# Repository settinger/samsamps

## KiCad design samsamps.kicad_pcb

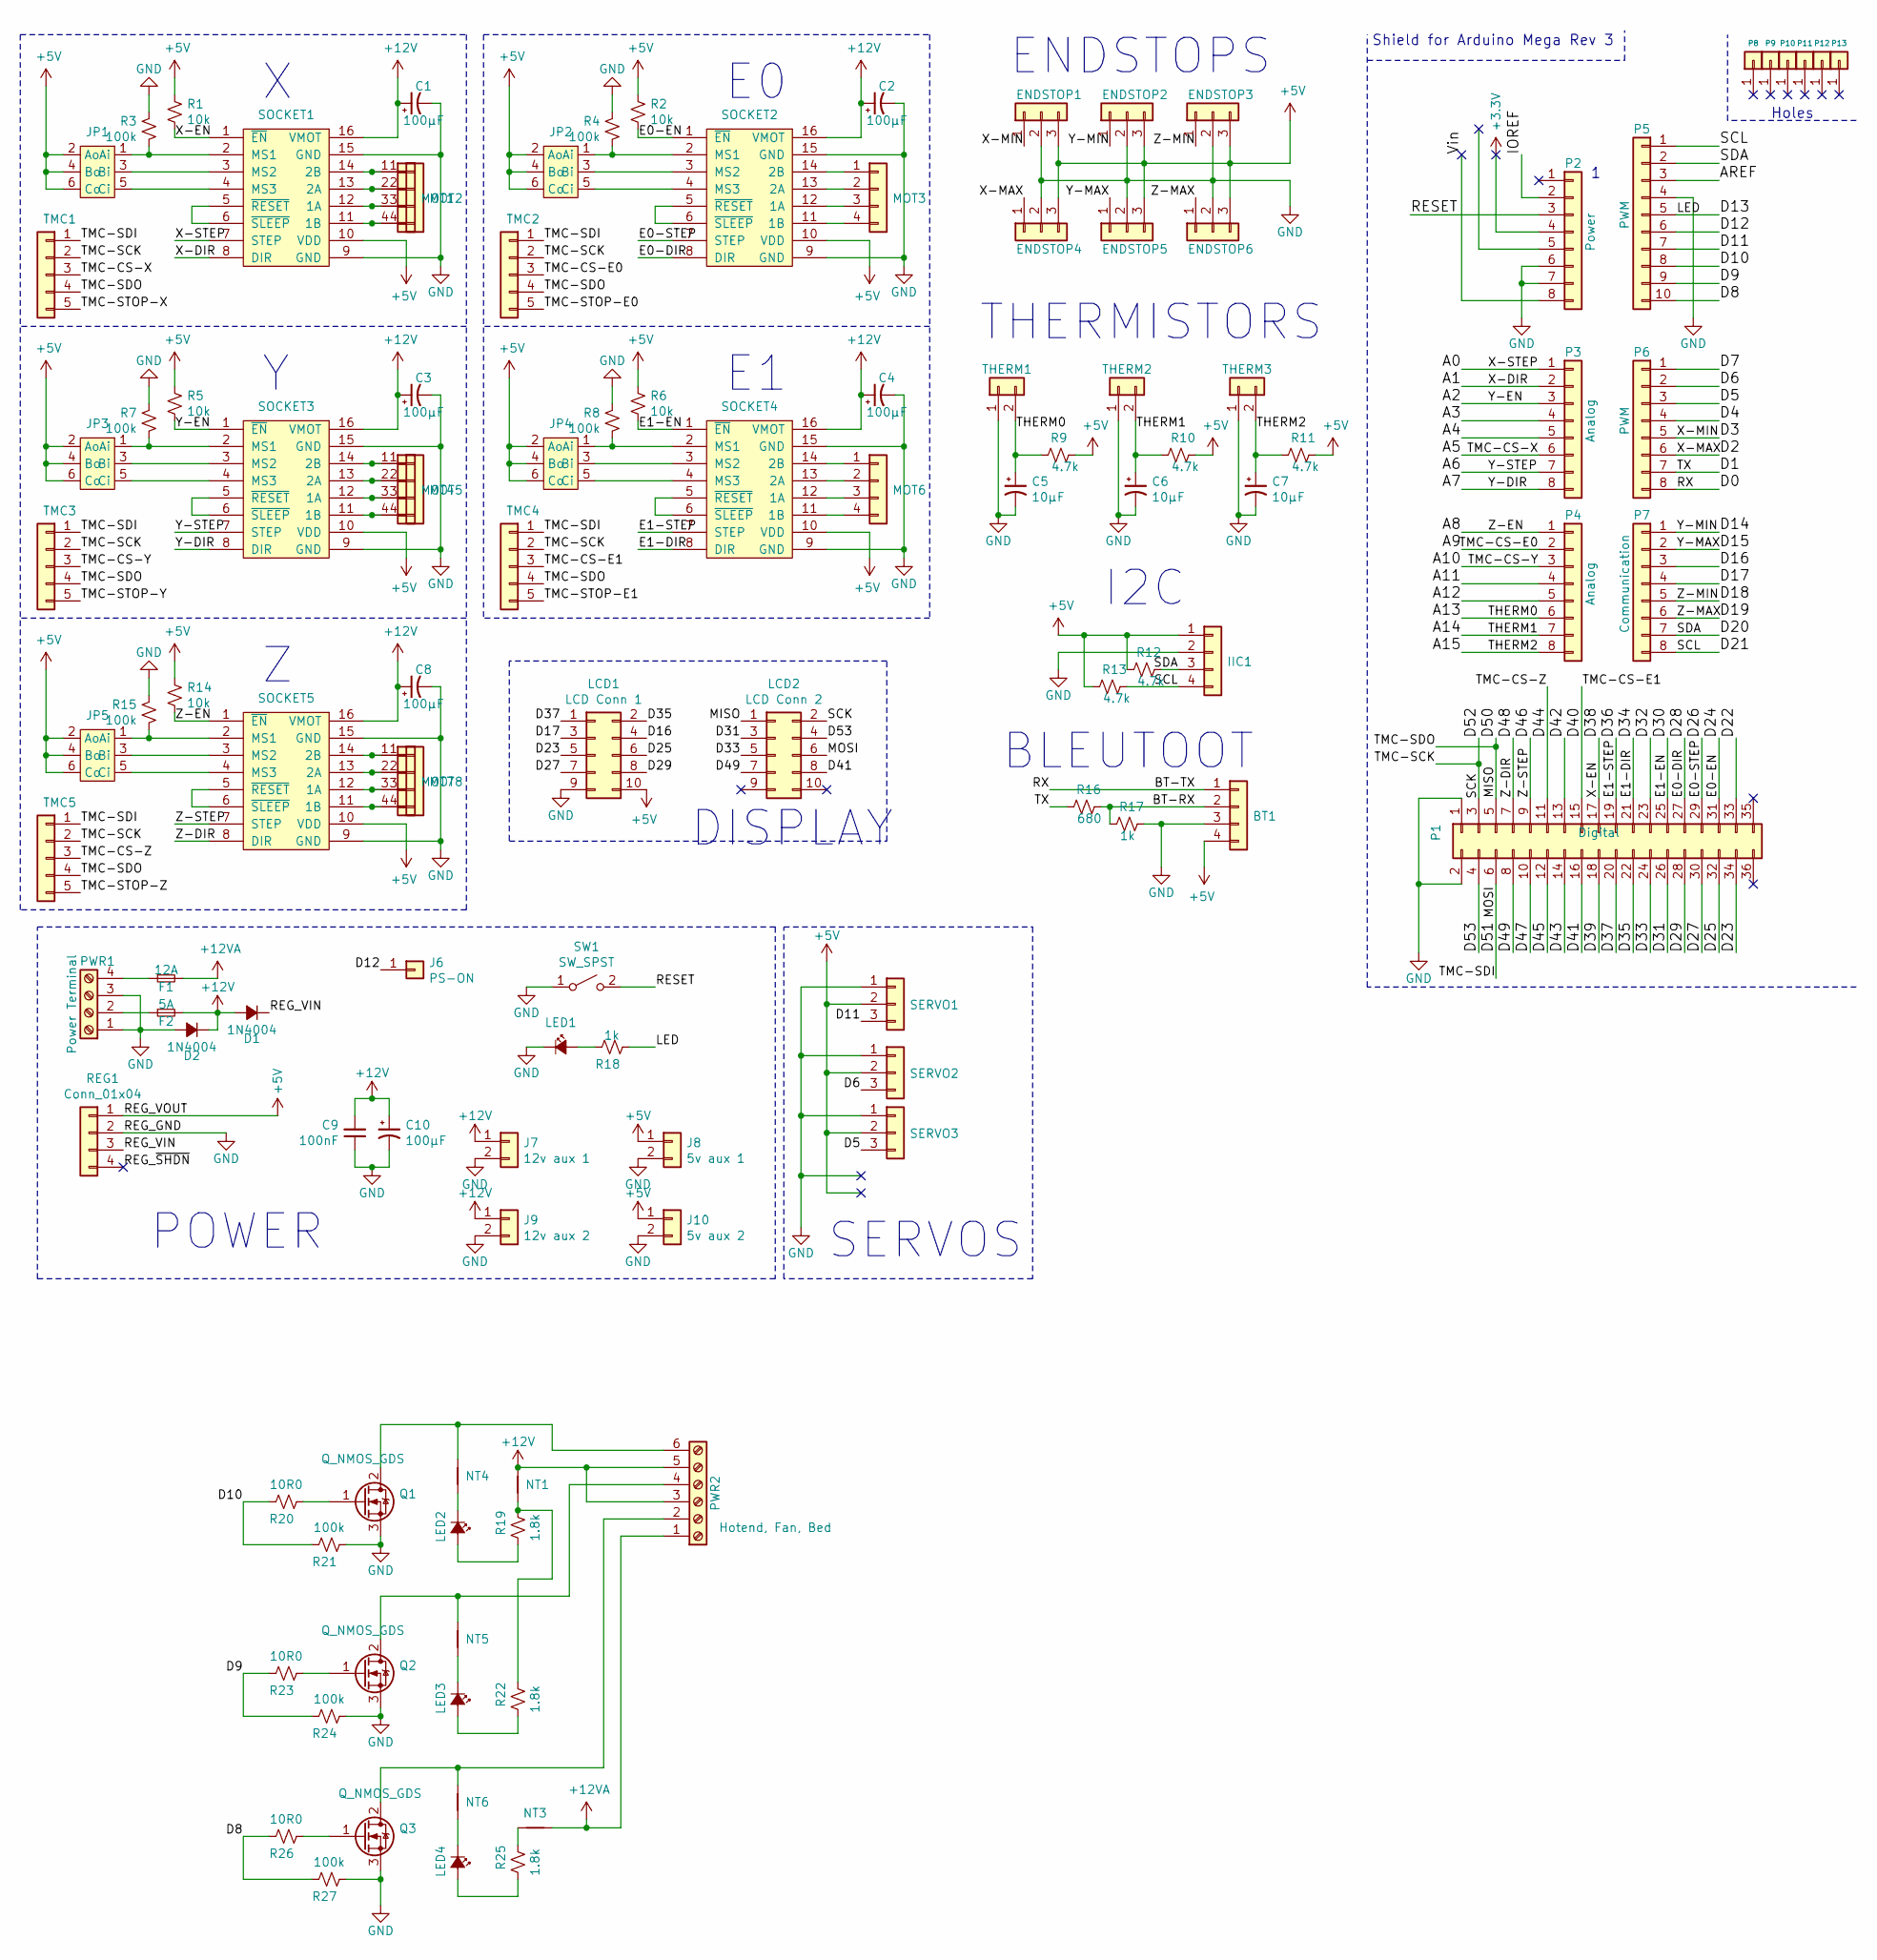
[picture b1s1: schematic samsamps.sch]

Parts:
BT1: Conn_01x04; Socket_Strip_Straight_1x04_Pitch2.54mm
C1, C2, C3, C4, C8, C10: 100μF; CP_Radial_D6.3mm_P2.50mm
C5, C6, C7: 10μF; CP_Radial_D6.3mm_P2.50mm
C9: 100nF; C_Rect_L7.0mm_W2.0mm_P5.00mm
D1, D2: 1N4004; D_5W_P10.16mm_Horizontal
ENDSTOP1, ENDSTOP2, ENDSTOP3, ENDSTOP4, ENDSTOP5, ENDSTOP6: Conn_01x03; Pin_Header_Straight_1x03_Pitch2.54mm
F1: 12A; Fuseholder5x20_horiz_SemiClosed_Casing10x25mm
F2: 5A; Fuseholder5x20_horiz_SemiClosed_Casing10x25mm
IIC1: Conn_01x04; Socket_Strip_Straight_1x04_Pitch2.54mm
J6: PS-ON; Pin_Header_Straight_1x01_Pitch2.54mm
J7: 12v aux 1; Socket_Strip_Straight_1x02_Pitch2.54mm
J8: 5v aux 1; Socket_Strip_Straight_1x02_Pitch2.54mm
J9: 12v aux 2; Socket_Strip_Straight_1x02_Pitch2.54mm
J10: 5v aux 2; Socket_Strip_Straight_1x02_Pitch2.54mm
JP1, JP2, JP3, JP4, JP5: jumpers; Pin_Header_Straight_2x03_Pitch2.54mm
LCD1: LCD Conn 1; Multicomp_MC9A12-1034_2x05x2.54mm_Straight
LCD2: LCD Conn 2; Multicomp_MC9A12-1034_2x05x2.54mm_Straight
LED1, LED2, LED3, LED4: LED_Small_ALT; LED_D3.0mm
MOT1, MOT2, MOT3, MOT4, MOT5, MOT6, MOT7, MOT8: Conn_01x04; Socket_Strip_Straight_1x04_Pitch2.54mm
NT1, NT3, NT4, NT5, NT6: Net-Tie_2; NetTie-2_SMD_Pad0.5mm
P1: Digital; Socket_Strip_Arduino_2x18
P2: Power; Socket_Strip_Arduino_1x08
P3, P4: Analog; Socket_Strip_Arduino_1x08
P5: PWM; Socket_Strip_Arduino_1x10
P6: PWM; Socket_Strip_Arduino_1x08
P7: Communication; Socket_Strip_Arduino_1x08
P8, P9, P10, P11, P12, P13: CONN_01X01; Arduino_1pin
PWR1: Power Terminal; TerminalBlock_4_P9.5mm
PWR2: Hotend, Fan, Bed; TerminalBlock_6_P9.5mm
Q1, Q2, Q3: Q_NMOS_GDS; TO-220-3_Vertical
R1, R2, R5, R6, R14: 10k; R_Axial_DIN0204_L3.6mm_D1.6mm_P7.62mm_Horizontal
R3, R4, R7, R8, R15, R21, R24, R27: 100k; R_Axial_DIN0204_L3.6mm_D1.6mm_P7.62mm_Horizontal
R9, R10, R11, R12, R13: 4.7k; R_Axial_DIN0204_L3.6mm_D1.6mm_P7.62mm_Horizontal
R16: 680; R_Axial_DIN0204_L3.6mm_D1.6mm_P7.62mm_Horizontal
R17, R18: 1k; R_Axial_DIN0204_L3.6mm_D1.6mm_P7.62mm_Horizontal
R19, R22, R25: 1.8k; R_Axial_DIN0204_L3.6mm_D1.6mm_P7.62mm_Horizontal
R20, R23, R26: 10R0; R_Axial_DIN0204_L3.6mm_D1.6mm_P7.62mm_Horizontal
REG1: Conn_01x04; Socket_Strip_Straight_1x04_Pitch2.54mm
SERVO1, SERVO2, SERVO3: Conn_01x03; Socket_Strip_Straight_1x03_Pitch2.54mm
SOCKET1, SOCKET2, SOCKET3, SOCKET4, SOCKET5: stepper_driver_socket; Stepper_Motor_Driver_Socket
SW1: SW_SPST; SW_PUSH_6mm
THERM1, THERM2, THERM3: Conn_01x02; Pin_Header_Straight_1x02_Pitch2.54mm
TMC1, TMC2, TMC3, TMC4, TMC5: Conn_01x05; Pin_Header_Straight_1x05_Pitch2.54mm

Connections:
+3V3: P2.4
+5V: BT1.4, ENDSTOP1.3, ENDSTOP2.3, ENDSTOP3.3, ENDSTOP4.3, ENDSTOP5.3, ENDSTOP6.3, IIC1.1, J8.1, J10.1, JP1.2 (Ao), JP1.4 (Bo), JP1.6 (Co), JP2.2 (Ao), JP2.4 (Bo), JP2.6 (Co), JP3.2 (Ao), JP3.4 (Bo), JP3.6 (Co), JP4.2 (Ao), JP4.4 (Bo), JP4.6 (Co), JP5.2 (Ao), JP5.4 (Bo), JP5.6 (Co), LCD1.10, R1.1, R2.1, R5.1, R6.1, R9.1, R10.1, R11.1, R12.2, R13.2, R14.1, REG1.1, SERVO1.2, SERVO2.2, SERVO3.2, SOCKET1.10 (VDD), SOCKET2.10 (VDD), SOCKET3.10 (VDD), SOCKET4.10 (VDD), SOCKET5.10 (VDD)
+12V: C1.1, C2.1, C3.1, C4.1, C8.1, C9.2, C10.1, D1.2 (A), D2.1 (K), F2.2, J7.1, J9.1, NT1.1, PWR2.3, PWR2.5, SOCKET1.16 (VMOT), SOCKET2.16 (VMOT), SOCKET3.16 (VMOT), SOCKET4.16 (VMOT), SOCKET5.16 (VMOT); also elsewhere on the board
+12VA: F1.2, NT3.2, PWR2.1
/A0: P3.1, SOCKET1.7 (STEP)
/A1: P3.2, SOCKET1.8 (DIR)
/A2: P3.3, R5.2, SOCKET3.1 (~EN)
/A3: P3.4
/A4: P3.5
/A5: P3.6, TMC1.3
/A6: P3.7, SOCKET3.7 (STEP)
/A7: P3.8, SOCKET3.8 (DIR)
/A8: P4.1, R14.2, SOCKET5.1 (~EN)
/A9: P4.2, TMC2.3
/A10: P4.3, TMC3.3
/A11: P4.4
/A12: P4.5
/A13: C5.1, P4.6, R9.2, THERM1.2
/A14: C6.1, P4.7, R10.2, THERM2.2
/A15: C7.1, P4.8, R11.2, THERM3.2
/AREF: P5.3
/BT-RX: BT1.2, R16.1, R17.2
/BT-TX: BT1.1, P6.8
/D1: P6.7, R16.2
/D2: ENDSTOP4.1, P6.6
/D3: ENDSTOP1.1, P6.5
/D4: P6.4
/D5: P6.3, SERVO3.3
/D6: P6.2, SERVO2.3
/D7: P6.1
/D8: P5.10, R26.1, R27.1
/D9: P5.9, R23.1, R24.1
/D10: P5.8, R20.1, R21.1
/D11: P5.7, SERVO1.3
/D12: J6.1, P5.6
/D13: P5.5, R18.2
/D14: ENDSTOP2.1, P7.1
/D15: ENDSTOP5.1, P7.2
/D16: LCD1.4, P7.3
/D17: LCD1.3, P7.4
/D18: ENDSTOP3.1, P7.5
/D19: ENDSTOP6.1, P7.6
/D20: IIC1.3, P5.2, P7.7, R12.1
/D21: IIC1.4, P5.1, P7.8, R13.1
/D22: P1.33
/D23: LCD1.5, P1.34
/D24: P1.31, R2.2, SOCKET2.1 (~EN)
/D25: LCD1.6, P1.32
/D26: P1.29, SOCKET2.7 (STEP)
/D27: LCD1.7, P1.30
/D28: P1.27, SOCKET2.8 (DIR)
/D29: LCD1.8, P1.28
/D30: P1.25, R6.2, SOCKET4.1 (~EN)
/D31: LCD2.3, P1.26
/D32: P1.23
/D33: LCD2.5, P1.24
/D34: P1.21, SOCKET4.8 (DIR)
/D35: LCD1.2, P1.22
/D36: P1.19, SOCKET4.7 (STEP)
/D37: LCD1.1, P1.20
/D38: P1.17, R1.2, SOCKET1.1 (~EN)
/D39: P1.18
/D40: P1.15, TMC4.3
/D41: LCD2.8, P1.16
/D42: P1.13
/D43: P1.14
/D44: P1.11, TMC5.3
/D45: P1.12
/D46: P1.9, SOCKET5.7 (STEP)
/D47: P1.10
/D48: P1.7, SOCKET5.8 (DIR)
/D49: LCD2.7, P1.8
/D50: LCD2.1, P1.5, TMC1.4, TMC2.4, TMC3.4, TMC4.4, TMC5.4
/D51: LCD2.6, P1.6, TMC1.1, TMC2.1, TMC3.1, TMC4.1, TMC5.1
/D52: LCD2.2, P1.3, TMC1.2, TMC2.2, TMC3.2, TMC4.2, TMC5.2
/D53: LCD2.4, P1.4
/IOREF: P2.2
/REG_VIN: D1.1 (K), REG1.3
/REG_~SHDN: REG1.4
/RESET: P2.3, SW1.2 (B)
/TMC-STOP-E0: TMC2.5
/TMC-STOP-E1: TMC4.5
/TMC-STOP-X: TMC1.5
/TMC-STOP-Y: TMC3.5
/TMC-STOP-Z: TMC5.5
/Vin: P2.8
GND: BT1.3, C1.2, C2.2, C3.2, C4.2, C5.2, C6.2, C7.2, C8.2, C9.1, C10.2, D2.2 (A), ENDSTOP1.2, ENDSTOP2.2, ENDSTOP3.2, ENDSTOP4.2, ENDSTOP5.2, ENDSTOP6.2, IIC1.2, J7.2, J8.2, J9.2, J10.2, LCD1.9, LED1.1 (K), P1.1, P1.2, P2.6, P2.7, P5.4, PWR1.1, PWR1.3, Q1.3 (S), Q2.3 (S), Q3.3 (S), R3.2, R4.2, R7.2, R8.2, R15.2, R17.1, R21.2, R24.2, R27.2, REG1.2, SERVO1.1, SERVO2.1, SERVO3.1, SOCKET1.9 (GND), SOCKET1.15 (GND), SOCKET2.9 (GND), SOCKET2.15 (GND), SOCKET3.9 (GND), SOCKET3.15 (GND), SOCKET4.9 (GND), SOCKET4.15 (GND), SOCKET5.9 (GND), SOCKET5.15 (GND), SW1.1 (A), THERM1.1, THERM2.1, THERM3.1
unnamed: F1.1, PWR1.4
unnamed: F2.1, PWR1.2
unnamed: JP1.1 (Ai), R3.1, SOCKET1.2 (MS1)
unnamed: JP1.3 (Bi), SOCKET1.3 (MS2)
unnamed: JP1.5 (Ci), SOCKET1.4 (MS3)
unnamed: JP2.1 (Ai), R4.1, SOCKET2.2 (MS1)
unnamed: JP2.3 (Bi), SOCKET2.3 (MS2)
unnamed: JP2.5 (Ci), SOCKET2.4 (MS3)
unnamed: JP3.1 (Ai), R7.1, SOCKET3.2 (MS1)
unnamed: JP3.3 (Bi), SOCKET3.3 (MS2)
unnamed: JP3.5 (Ci), SOCKET3.4 (MS3)
unnamed: JP4.1 (Ai), R8.1, SOCKET4.2 (MS1)
unnamed: JP4.3 (Bi), SOCKET4.3 (MS2)
unnamed: JP4.5 (Ci), SOCKET4.4 (MS3)
unnamed: JP5.1 (Ai), R15.1, SOCKET5.2 (MS1)
unnamed: JP5.3 (Bi), SOCKET5.3 (MS2)
unnamed: JP5.5 (Ci), SOCKET5.4 (MS3)
unnamed: LED1.2 (A), R18.1
unnamed: LED2.1 (K), NT4.2
unnamed: LED2.2 (A), R19.2
unnamed: LED3.1 (K), NT5.2
unnamed: LED3.2 (A), R22.2
unnamed: LED4.1 (K), NT6.2
unnamed: LED4.2 (A), R25.2
unnamed: MOT1.1, MOT2.1, SOCKET1.14 (2B)
unnamed: MOT1.2, MOT2.2, SOCKET1.13 (2A)
unnamed: MOT1.3, MOT2.3, SOCKET1.12 (1A)
unnamed: MOT1.4, MOT2.4, SOCKET1.11 (1B)
unnamed: MOT3.1, SOCKET2.14 (2B)
unnamed: MOT3.2, SOCKET2.13 (2A)
unnamed: MOT3.3, SOCKET2.12 (1A)
unnamed: MOT3.4, SOCKET2.11 (1B)
unnamed: MOT4.1, MOT5.1, SOCKET3.14 (2B)
unnamed: MOT4.2, MOT5.2, SOCKET3.13 (2A)
unnamed: MOT4.3, MOT5.3, SOCKET3.12 (1A)
unnamed: MOT4.4, MOT5.4, SOCKET3.11 (1B)
unnamed: MOT6.1, SOCKET4.14 (2B)
unnamed: MOT6.2, SOCKET4.13 (2A)
unnamed: MOT6.3, SOCKET4.12 (1A)
unnamed: MOT6.4, SOCKET4.11 (1B)
unnamed: MOT7.1, MOT8.1, SOCKET5.14 (2B)
unnamed: MOT7.2, MOT8.2, SOCKET5.13 (2A)
unnamed: MOT7.3, MOT8.3, SOCKET5.12 (1A)
unnamed: MOT7.4, MOT8.4, SOCKET5.11 (1B)
unnamed 133: NT1.2, R19.1, R22.1; also elsewhere on the board
unnamed: NT3.1, R25.1
unnamed: NT4.1, PWR2.6, Q1.2 (D)
unnamed: NT5.1, PWR2.4, Q2.2 (D)
unnamed: NT6.1, PWR2.2, Q3.2 (D)
unnamed: Q1.1 (G), R20.2
unnamed: Q2.1 (G), R23.2
unnamed: Q3.1 (G), R26.2
unnamed: SOCKET1.5 (~RESET), SOCKET1.6 (~SLEEP)
unnamed: SOCKET2.5 (~RESET), SOCKET2.6 (~SLEEP)
unnamed: SOCKET3.5 (~RESET), SOCKET3.6 (~SLEEP)
unnamed: SOCKET4.5 (~RESET), SOCKET4.6 (~SLEEP)
unnamed: SOCKET5.5 (~RESET), SOCKET5.6 (~SLEEP)

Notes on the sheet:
Shield for Arduino Mega Rev 3
Holes
POWER
DISPLAY
SERVOS
ENDSTOPS
THERMISTORS
I2C
BLEUTOOT

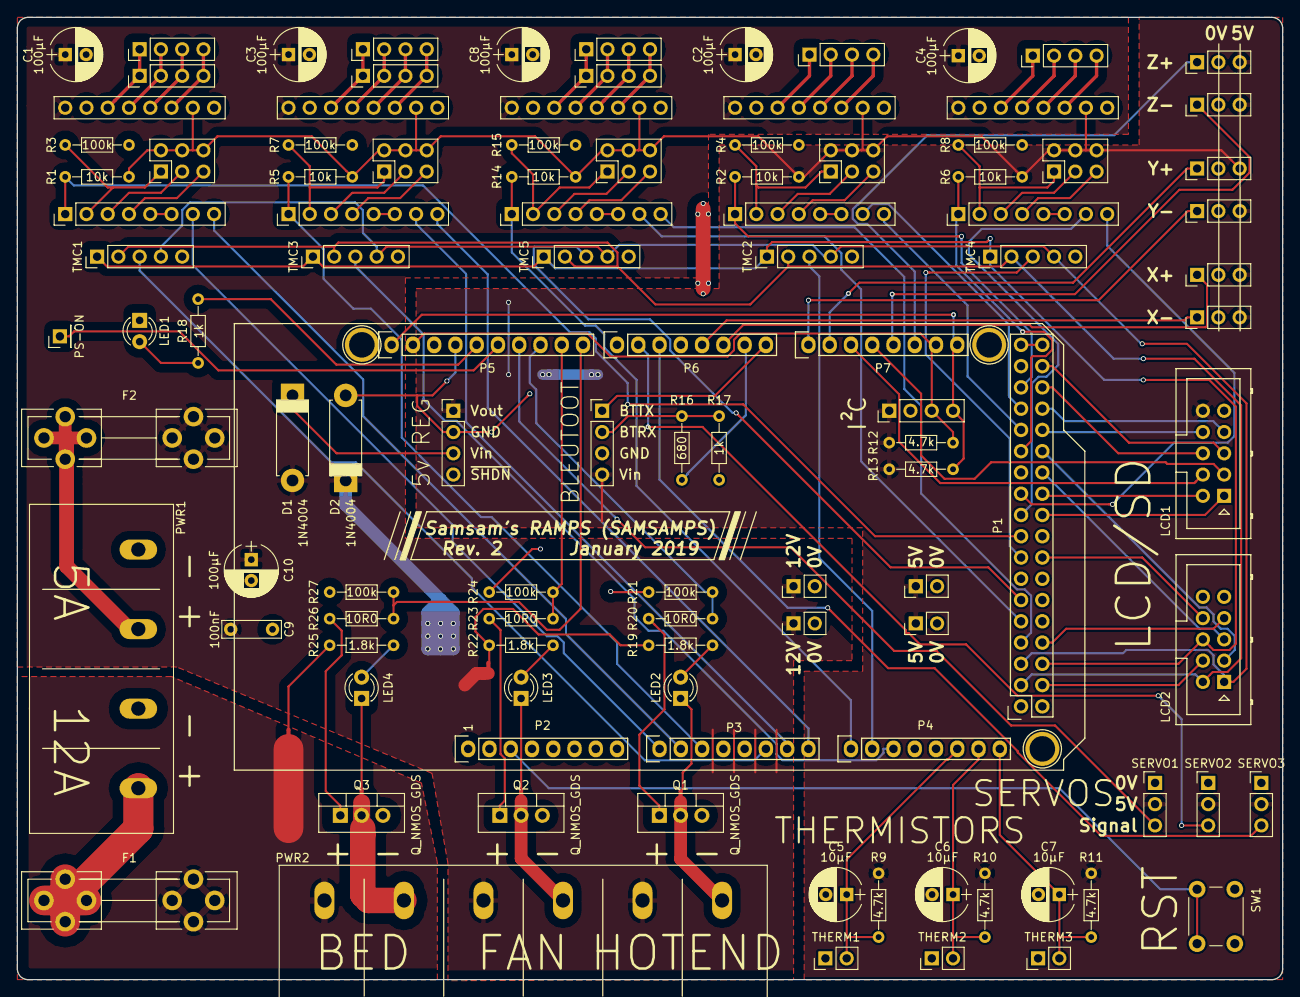
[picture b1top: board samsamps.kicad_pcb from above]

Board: 2 copper layers, 151.1 x 114.9 mm, 111 parts (0 on the bottom side), 121 nets.

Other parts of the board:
NT2: Net-Tie_2; NetTie-2_SMD_Pad0.5mm

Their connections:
+12V: NT2.2; also elsewhere on the board
unnamed 133: NT2.1; also elsewhere on the board

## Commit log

2019-02-16 SAMSAMPS Rev 2
